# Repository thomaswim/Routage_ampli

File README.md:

# Routage Ampli 
#### par Clémence Arnal et Thomas Boursac, 3 IMACS C

```
git clone https://github.com/thomaswim/Routage_ampli
```

Symbole Relay => Relay/Relay_1CT

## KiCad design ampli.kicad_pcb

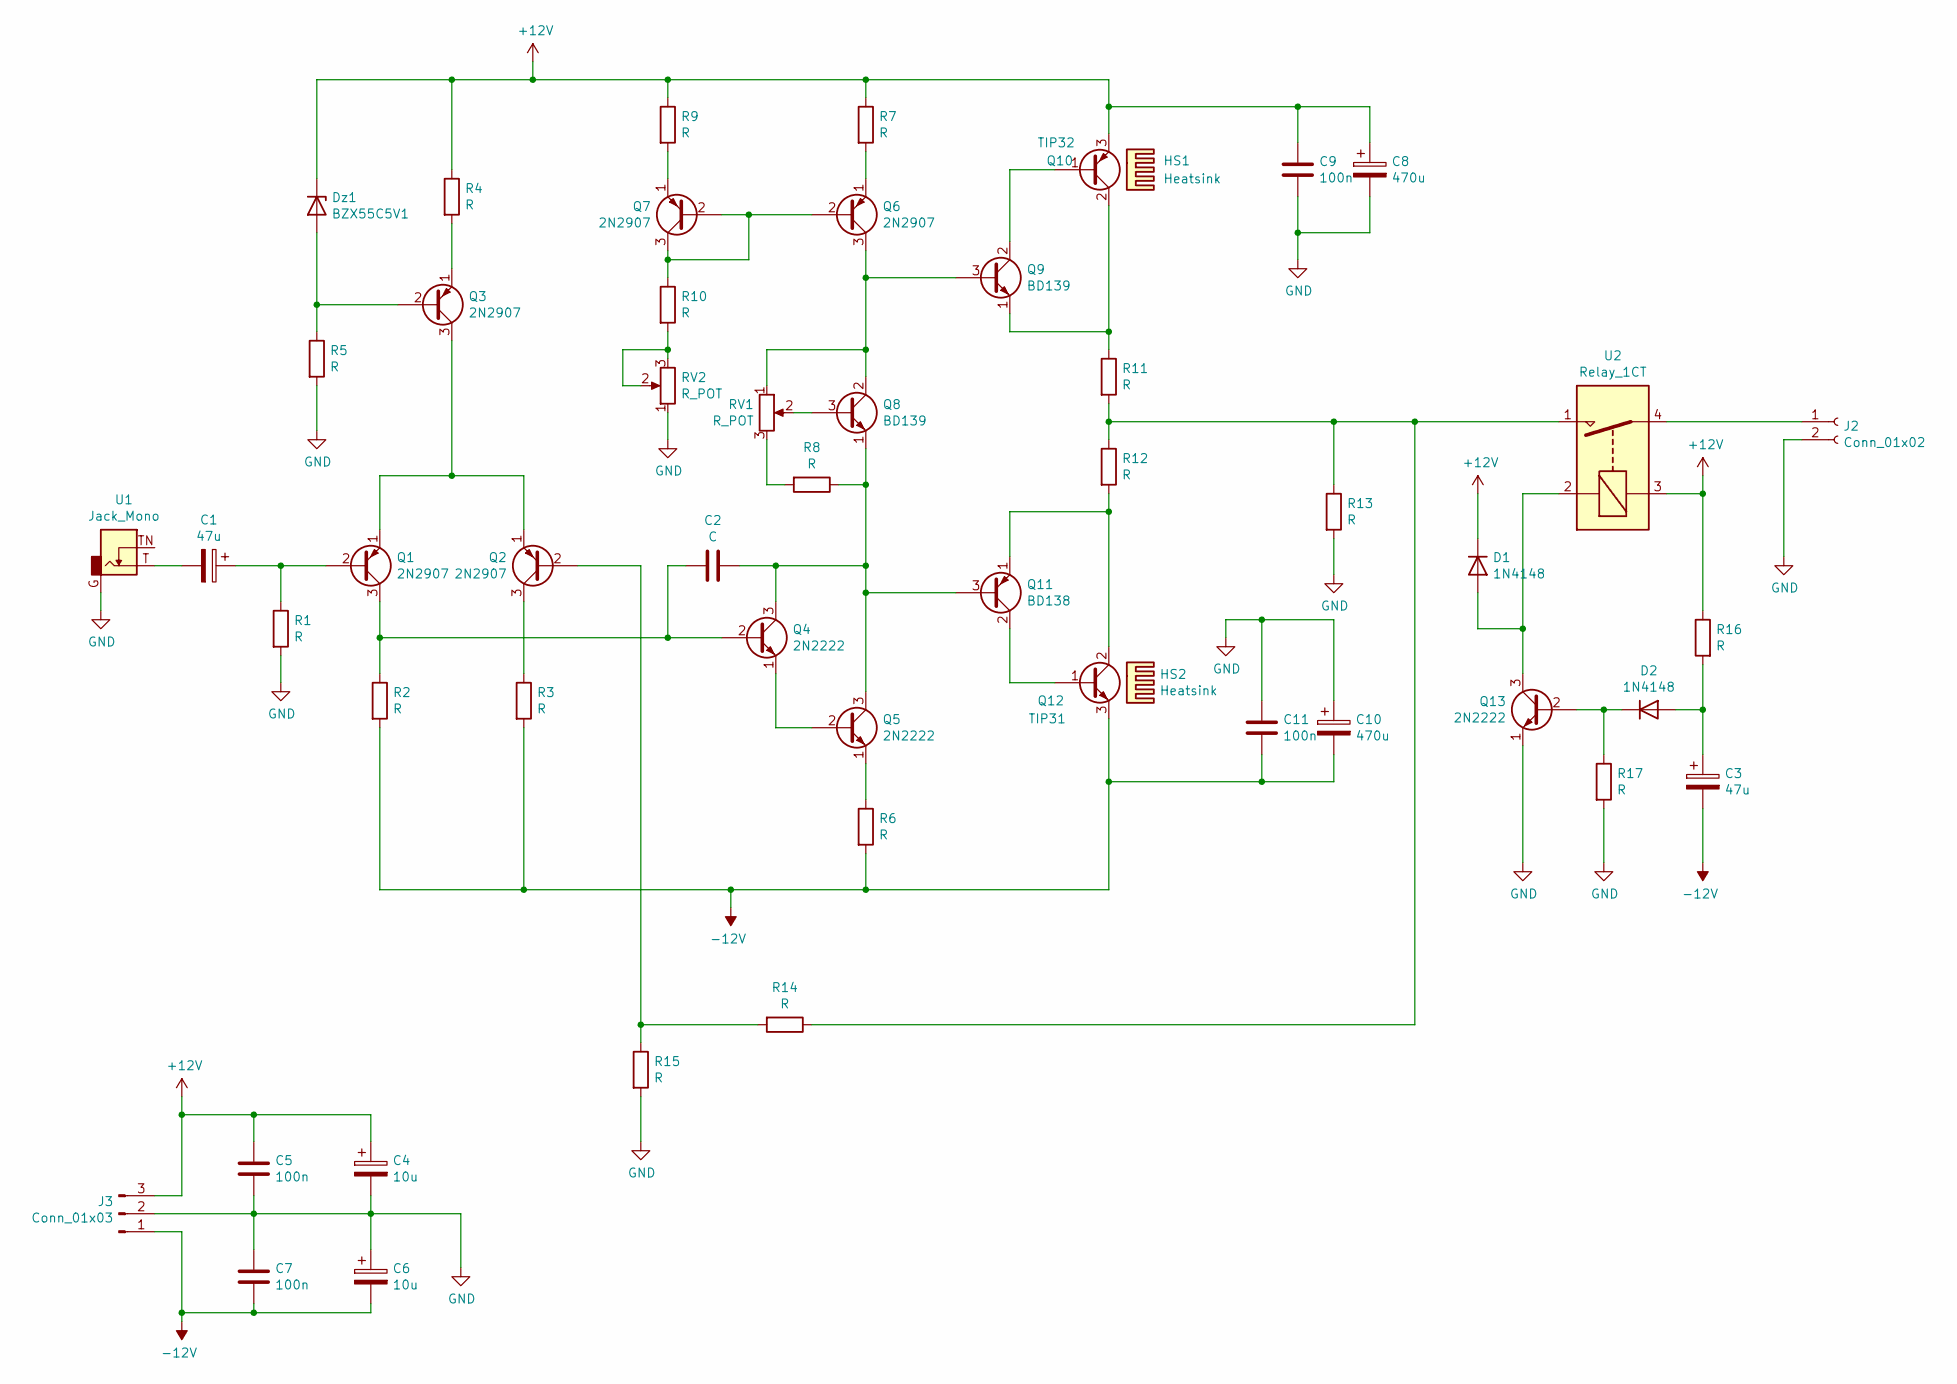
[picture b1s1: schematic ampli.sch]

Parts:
C1, C3: 47u; CP_Radial_D8.0mm_P5.00mm
C2: C; C_Rect_L7.2mm_W3.5mm_P5.00mm_FKS2_FKP2_MKS2_MKP2
C4, C6: 10u; CP_Radial_D8.0mm_P5.00mm
C5, C7, C9, C11: 100n; C_Rect_L7.2mm_W3.5mm_P5.00mm_FKS2_FKP2_MKS2_MKP2
C8, C10: 470u; CP_Radial_D12.5mm_P5.00mm
D1, D2: 1N4148; D_DO-35_SOD27_P10.16mm_Horizontal
Dz1: BZX55C5V1; D_DO-35_SOD27_P10.16mm_Horizontal
HS1, HS2: Heatsink; Heatsink_Fischer_SK104-STC-STIC_35x13mm_2xDrill2.5mm
J2: Conn_01x02; PhoenixContact_MSTBVA_2,5_2-G-5,08_1x02_P5.08mm_Vertical
J3: Conn_01x03; PhoenixContact_MSTBVA_2,5_3-G-5,08_1x03_P5.08mm_Vertical
Q1, Q2, Q3, Q6, Q7: 2N2907; TO-18-3
Q4, Q5, Q13: 2N2222; TO-18-3
Q8, Q9: BD139; TO-126-3_Vertical
Q10: TIP32; TO-220-3_Vertical
Q11: BD138; TO-126-3_Vertical
Q12: TIP31; TO-220-3_Vertical
R1, R2, R3, R4, R5, R6, R7, R8, R9, R10, R13, R14, R15, R16, R17: R; R_Axial_DIN0207_L6.3mm_D2.5mm_P10.16mm_Horizontal
R11, R12: R; R_Axial_DIN0516_L15.5mm_D5.0mm_P20.32mm_Horizontal
RV1, RV2: R_POT; Potentiometer_Bourns_3296W_Vertical
U1: Jack_Mono; Jack_35RAPC2AV
U2: Relay_1CT; OJ-SS-112HM.000_1

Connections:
+12V: C4.1, C5.1, C8.1, C9.1, D1.1 (K), Dz1.1 (K), J3.3, Q10.3 (E), R4.1, R7.1, R9.1, R16.1, U2.3
-12V: C3.2, C6.2, C7.2, C10.2, C11.2, J3.1, Q12.3 (E), R2.2, R3.2, R6.2
GND: C4.2, C5.2, C6.1, C7.1, C8.2, C9.2, C10.1, C11.1, J2.2, J3.2, Q13.1 (E), R1.2, R5.2, R13.2, R15.2, R17.2, RV2.1, U1.G
unnamed: C1.1, Q1.2 (B), R1.1
unnamed: C1.2, U1.T
unnamed: C2.1, Q4.3 (C), Q5.3 (C), Q8.1 (E), Q11.3 (B), R8.1
unnamed: C2.2, Q1.3 (C), Q4.2 (B), R2.1
unnamed: C3.1, D2.2 (A), R16.2
unnamed: D1.2 (A), Q13.3 (C), U2.2
unnamed: D2.1 (K), Q13.2 (B), R17.1
unnamed: Dz1.2 (A), Q3.2 (B), R5.1
unnamed: J2.1, U2.4
unnamed: Q1.1 (E), Q2.1 (E), Q3.3 (C)
unnamed: Q2.2 (B), R14.2, R15.1
unnamed: Q2.3 (C), R3.1
unnamed: Q3.1 (E), R4.2
unnamed: Q4.1 (E), Q5.2 (B)
unnamed: Q5.1 (E), R6.1
unnamed: Q6.1 (E), R7.2
unnamed: Q6.2 (B), Q7.2 (B), Q7.3 (C), R10.1
unnamed: Q6.3 (C), Q8.2 (C), Q9.3 (B), RV1.1
unnamed: Q7.1 (E), R9.2
unnamed: Q8.3 (B), RV1.2
unnamed: Q9.2 (C), Q10.1 (B)
unnamed: Q9.1 (E), Q10.2 (C), R11.1
unnamed: Q11.1 (E), Q12.2 (C), R12.2
unnamed: Q11.2 (C), Q12.1 (B)
unnamed: R8.2, RV1.3
unnamed: R10.2, RV2.2, RV2.3
unnamed: R11.2, R12.1, R13.1, R14.1, U2.1

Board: 2 copper layers, 52 parts (0 on the bottom side), 30 nets, no tracks yet.

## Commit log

2021-03-23 etape 1
2021-03-23 etape 1.2
2021-03-23 etape 1.3
2021-03-23 version 1.4
2021-03-23 test
2021-03-23 version 1.5
2021-03-29 version 1.6
2021-03-29 version 1.7
2021-04-08 version routage 1.0
2021-04-10 clem 1.0
2021-04-10 version4
2021-04-10 test 1.1
2021-04-10 placement 1
2021-04-10 placement2
